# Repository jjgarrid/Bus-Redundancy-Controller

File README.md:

# Bus-Redundancy-Controller
Bus redundancy controller PoC implemented using a FPGA

This project is in a very early stage of design.

The idea comes from an academic paper:

https://www.researchgate.net/publication/262367702_Design_of_redundant_CAN_bus_for_telemetry_and_telecommand_subsystem_of_a_micro-satellite

Design of Redundant CAN Bus for Telemetry and Telecommand Subsystem of a Micro-Satellite

## The idea

Connect several buses common buses (Spacewire, CAN, I2C, SPI...) to a inexpensive, small, low power FPGA (Lattice semi ICE40) that will provide smart switching between different redundant routes (physical traces in the board).

## Constraints / requirements

FPGA needs to be small and integrated in order to be easily added to on board computers and other systems. Good candidates are ICE40LP640 or ICE40LP1K in the package configuration 16-ball WLCSP (1.40 x 1.48 mm). 

Future developments might consider devices with more IO banks.

## Hardware develpment

Either KiCad or Upverter. Probably upverter as it is an online solution.

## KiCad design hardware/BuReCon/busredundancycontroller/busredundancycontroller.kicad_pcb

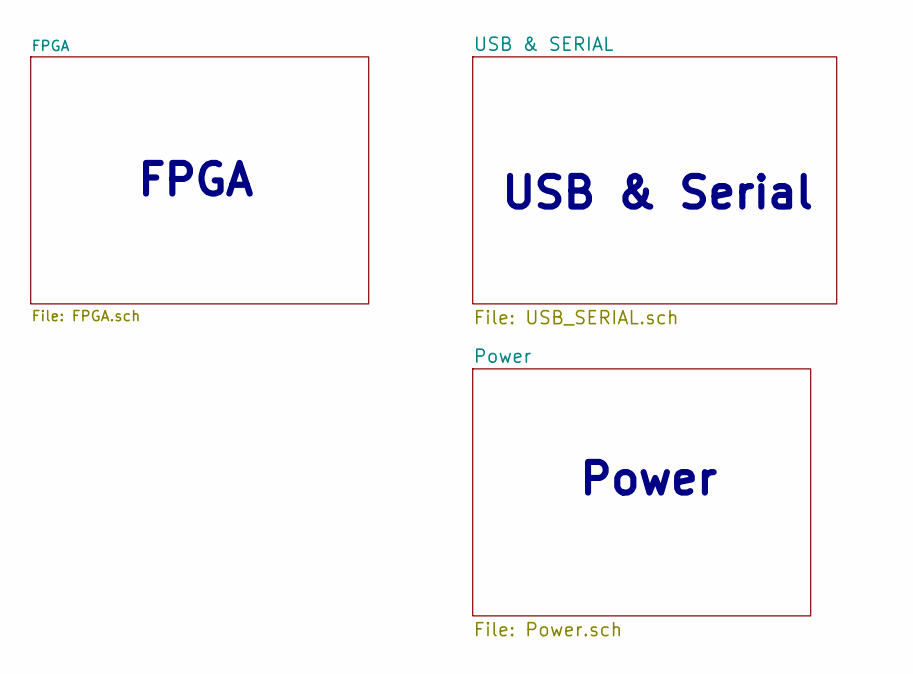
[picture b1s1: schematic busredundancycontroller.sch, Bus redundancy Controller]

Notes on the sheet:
Power
USB & Serial
FPGA

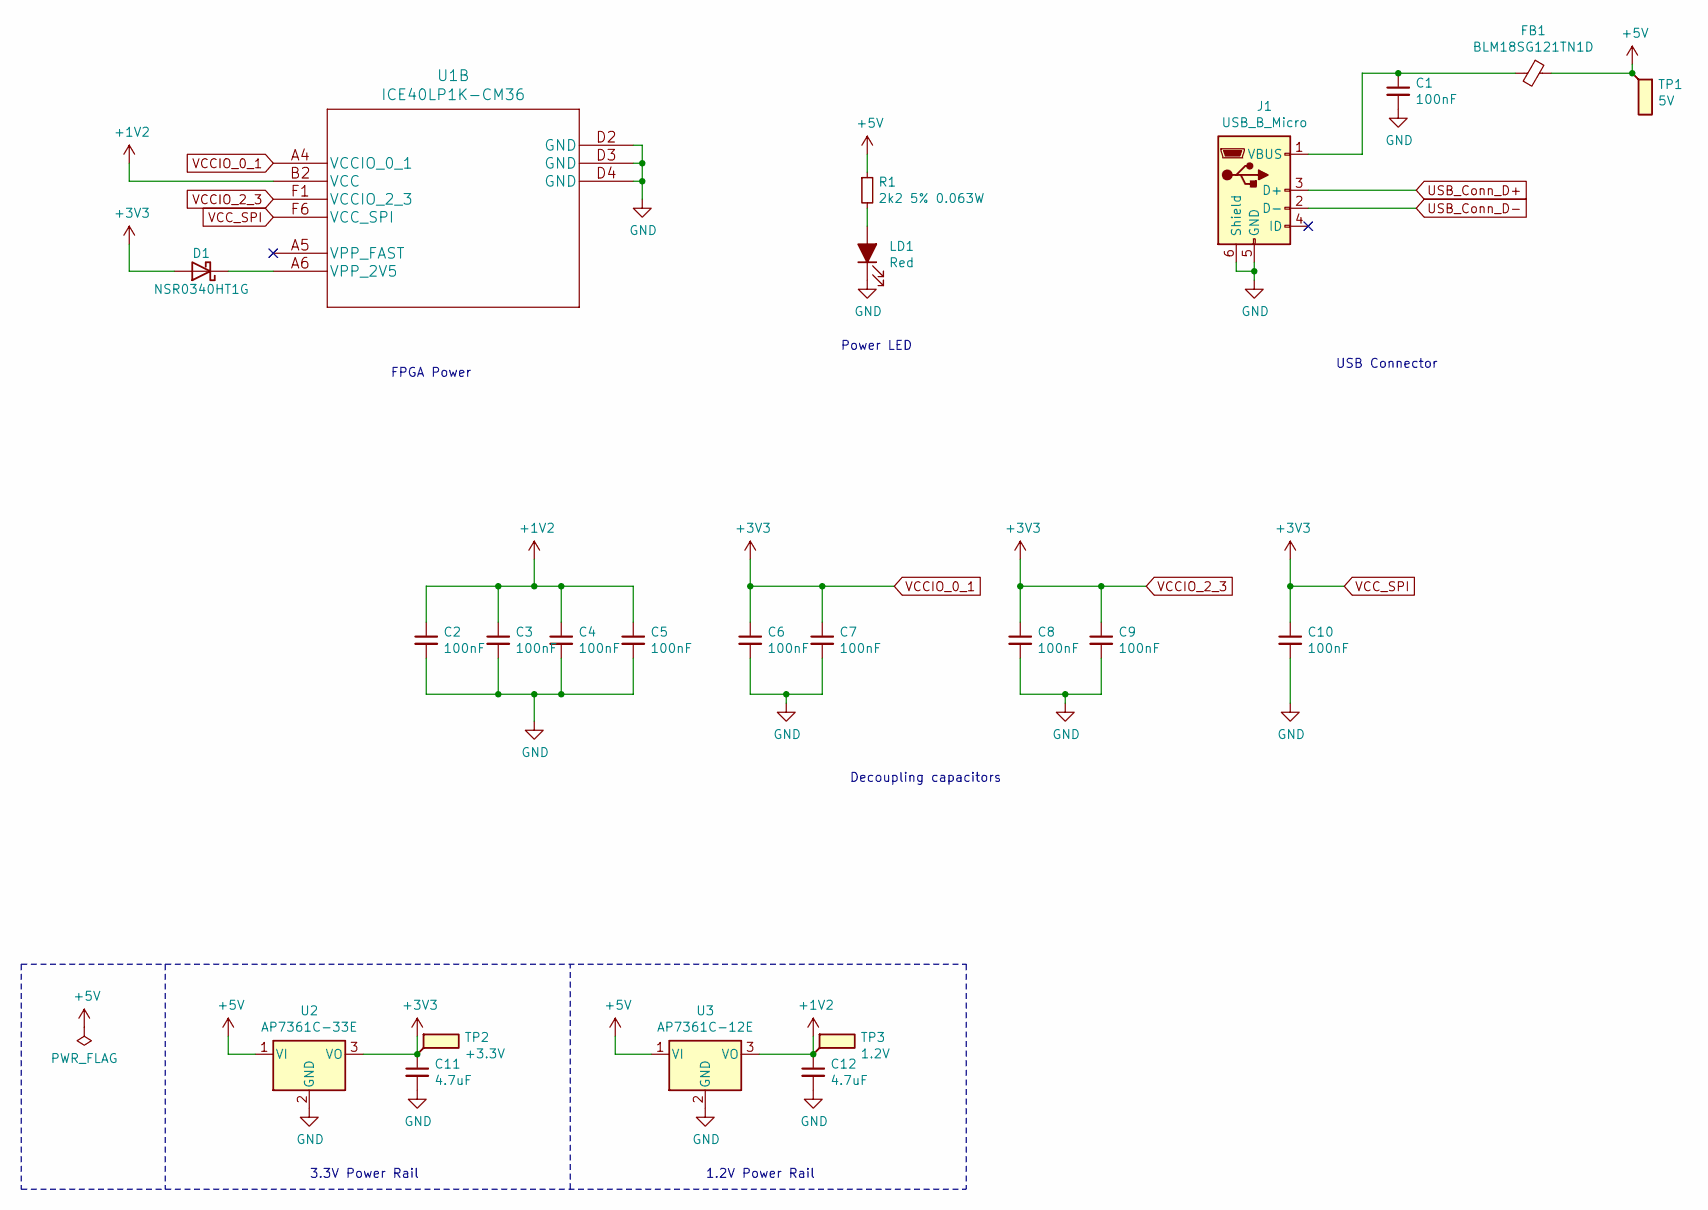
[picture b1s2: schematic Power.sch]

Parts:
C1, C2, C3, C4, C5, C6, C7, C8, C9, C10: 100nF; C_0603_1608Metric
C11, C12: 4.7uF; C_0603_1608Metric
D1: NSR0340HT1G; D_SOD-323
FB1: BLM18SG121TN1D; L_0603_1608Metric
J1: USB_B_Micro; USB_Micro-AB_Molex_47590-0001
LD1: Red; LED_0603_1608Metric
R1: 2k2 5% 0.063W; R_0603_1608Metric
TP1: 5V; TestPoint_Pad_D1.0mm
TP2: +3.3V; TestPoint_Pad_D1.0mm
TP3: 1.2V; TestPoint_Pad_D1.0mm
U1: ICE40LP1K-CM36
U2: AP7361C-33E; SOT-223
U3: AP7361C-12E; SOT-223

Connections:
+1V2: C2.1, C3.1, C4.1, C5.1, C12.1, TP3.1, U1.B2 (VCC), U3.3 (VO)
+5V: FB1.1, R1.1, TP1.1, U2.1 (VI), U3.1 (VI); also elsewhere on the board
GND: C1.2, C2.2, C3.2, C4.2, C5.2, C6.2, C7.2, C8.2, C9.2, C10.2, C11.2, C12.2, J1.5 (GND), J1.6 (Shield), LD1.1 (K), U1.D2 (GND), U1.D3 (GND), U1.D4 (GND), U2.2 (GND), U3.2 (GND); also elsewhere on the board
unnamed: C1.1, FB1.2, J1.1 (VBUS)
unnamed: D1.1 (K), U1.A6 (VPP_2V5)
unnamed: LD1.2 (A), R1.2
USB_Conn_D+: J1.3 (D+); also elsewhere on the board
USB_Conn_D-: J1.2 (D-); also elsewhere on the board

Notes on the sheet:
3.3V Power Rail
1.2V Power Rail
Decoupling capacitors
USB Connector
FPGA Power
Power LED

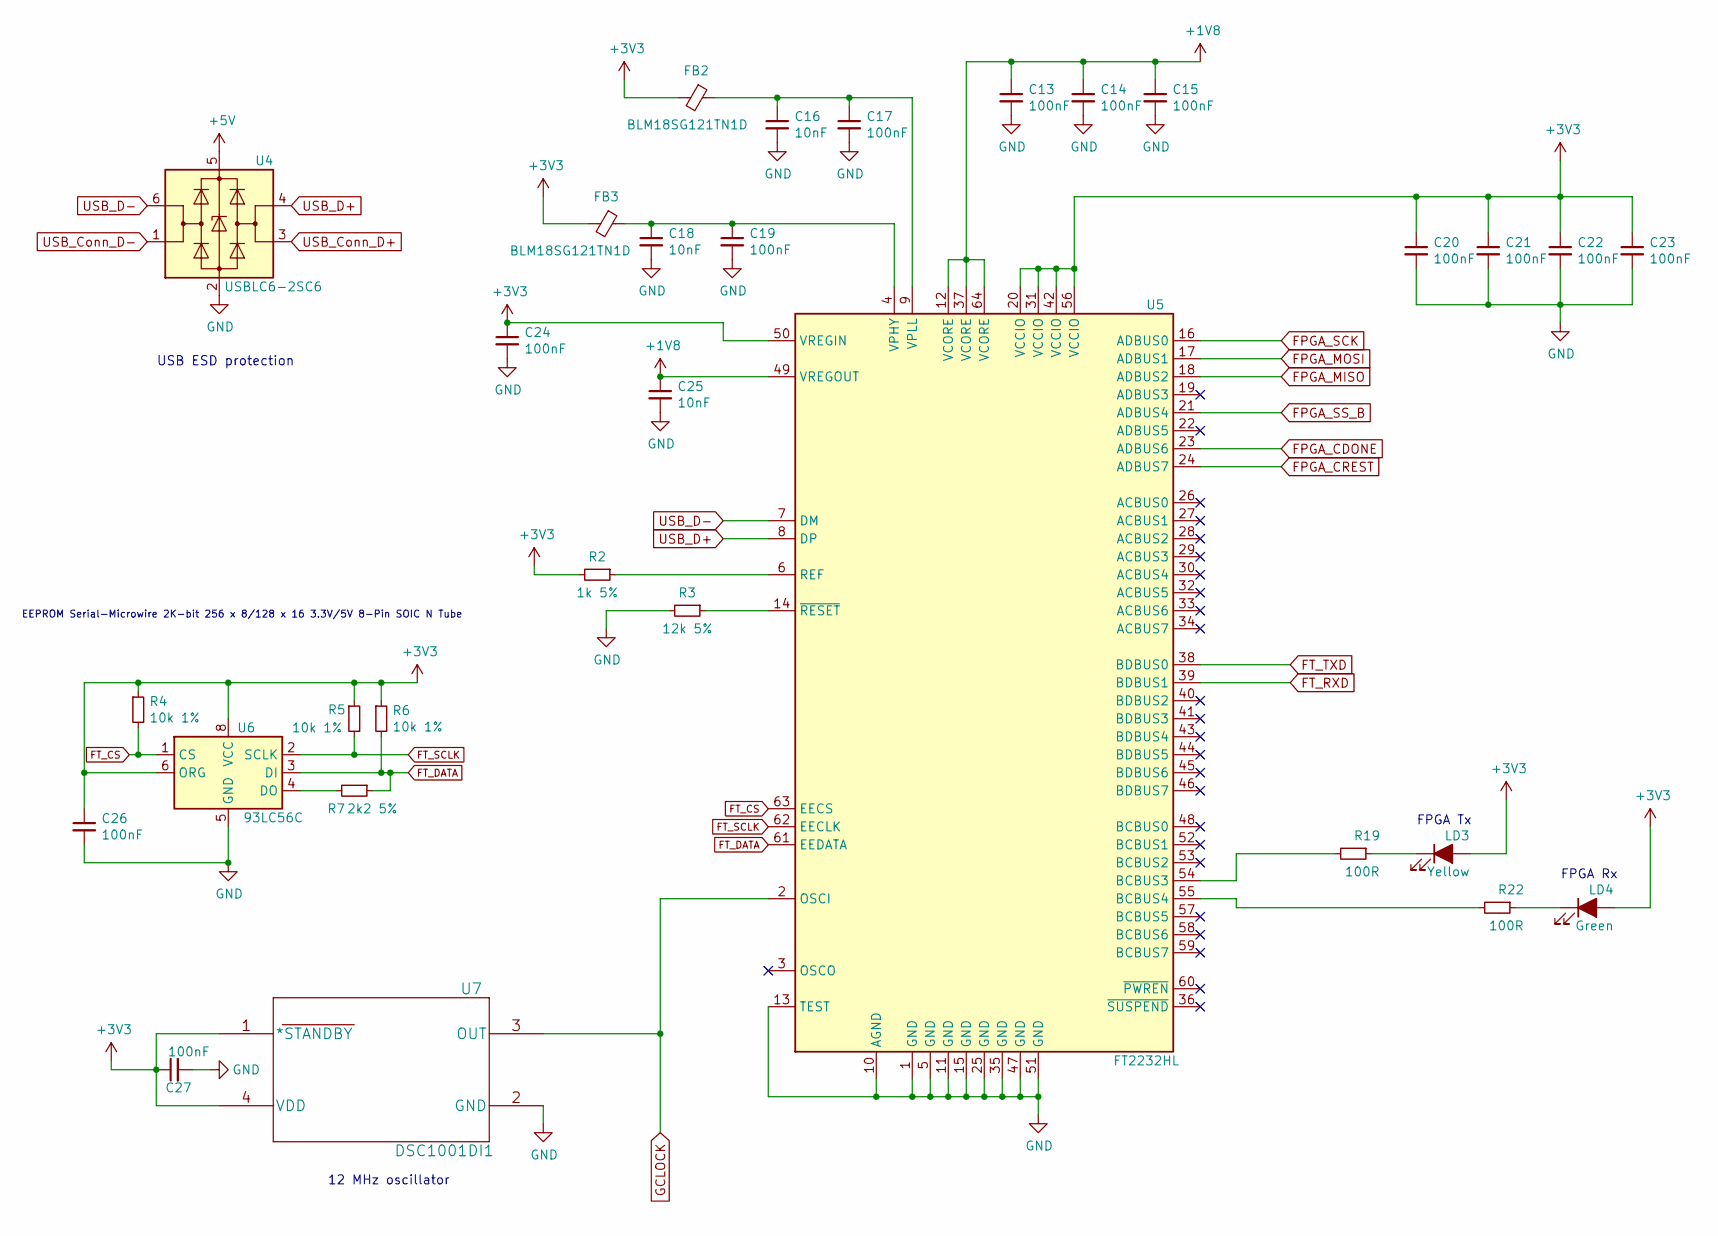
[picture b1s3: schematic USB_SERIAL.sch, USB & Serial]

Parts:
C13, C14, C15, C17, C19, C20, C21, C22, C23, C24, C26, C27: 100nF; C_0603_1608Metric
C16, C18, C25: 10nF; C_0603_1608Metric
FB2, FB3: BLM18SG121TN1D; L_0603_1608Metric
LD3: Yellow; LED_0603_1608Metric
LD4: Green; LED_0603_1608Metric
R2: 1k 5%; R_0603_1608Metric
R3: 12k 5%; R_0603_1608Metric
R4, R5, R6: 10k 1%; R_0603_1608Metric
R7: 2k2 5%; R_0603_1608Metric
R19, R22: 100R; R_0603_1608Metric
U4: USBLC6-2SC6; SOT-23-6
U5: FT2232HL; LQFP-64_10x10mm_P0.5mm
U6: 93LC56C; SOIC-8_3.9x4.9mm_P1.27mm
U7: DSC1001DI1; DSC1001DI1-033.3333T

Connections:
+1V8: C13.1, C14.1, C15.1, C25.1, U5.12 (VCORE), U5.37 (VCORE), U5.49 (VREGOUT), U5.64 (VCORE)
+5V: U4.5 (VBUS); also elsewhere on the board
FPGA_CDONE: U5.23 (ADBUS6); also elsewhere on the board
FPGA_CREST: U5.24 (ADBUS7); also elsewhere on the board
FPGA_MISO: U5.18 (ADBUS2); also elsewhere on the board
FPGA_MOSI: U5.17 (ADBUS1); also elsewhere on the board
FPGA_SCK: U5.16 (ADBUS0); also elsewhere on the board
FPGA_SS_B: U5.21 (ADBUS4); also elsewhere on the board
FT_CS: R4.2, U5.63 (EECS), U6.1 (CS)
FT_DATA: R6.2, R7.1, U5.61 (EEDATA), U6.3 (DI)
FT_SCLK: R5.2, U5.62 (EECLK), U6.2 (SCLK)
GCLOCK: U5.2 (OSCI), U7.3 (OUT); also elsewhere on the board
GND: C13.2, C14.2, C15.2, C16.2, C17.2, C18.2, C19.2, C20.2, C21.2, C22.2, C23.2, C24.2, C25.2, C26.2, C27.2, R3.2, U4.2 (GND), U5.1 (GND), U5.5 (GND), U5.10 (AGND), U5.11 (GND), U5.13 (TEST), U5.15 (GND), U5.25 (GND), U5.35 (GND), U5.47 (GND), U5.51 (GND), U6.5 (GND), U7.2 (GND); also elsewhere on the board
unnamed: C16.1, C17.1, FB2.1, U5.9 (VPLL)
unnamed: C18.1, C19.1, FB3.1, U5.4 (VPHY)
unnamed: LD3.1 (K), R19.1
unnamed: LD4.1 (K), R22.1
unnamed: R2.1, U5.6 (REF)
unnamed: R3.1, U5.14 (~RESET)
unnamed: R7.2, U6.4 (DO)
unnamed: R19.2, U5.54 (BCBUS3)
unnamed: R22.2, U5.55 (BCBUS4)
USB_Conn_D+: U4.3 (I/O2); also elsewhere on the board
USB_Conn_D-: U4.1 (I/O1); also elsewhere on the board
USB_D+: U4.4 (I/O2), U5.8 (DP)
USB_D-: U4.6 (I/O1), U5.7 (DM)

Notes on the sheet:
USB ESD protection
12 MHz oscillator
EEPROM Serial-Microwire 2K-bit 256 x 8/128 x 16 3.3V/5V 8-Pin SOIC N Tube
FPGA Tx
FPGA Rx

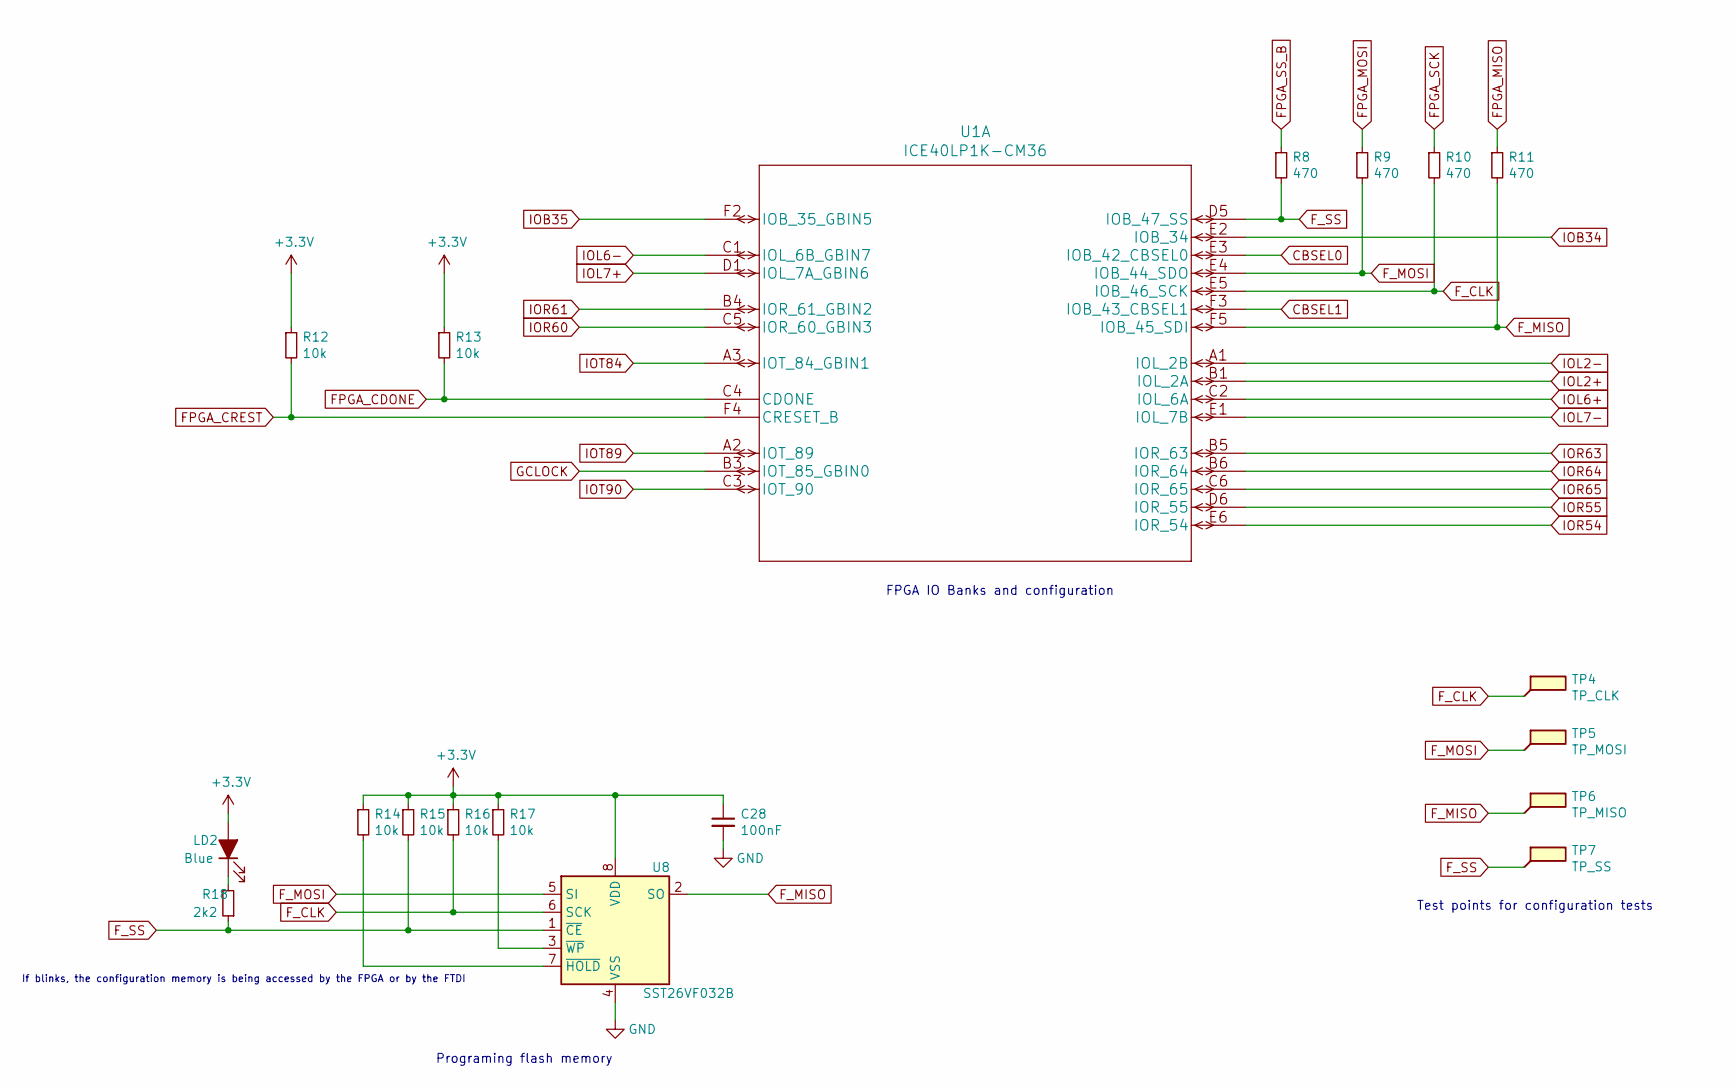
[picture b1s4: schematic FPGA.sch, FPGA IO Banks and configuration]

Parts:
C28: 100nF
LD2: Blue; LED_0201_0603Metric
R8, R9, R10, R11: 470
R12, R13, R14, R15, R16, R17: 10k
R18: 2k2
TP4: TP_CLK; TestPoint_Plated_Hole_D3.0mm
TP5: TP_MOSI; TestPoint_Plated_Hole_D3.0mm
TP6: TP_MISO; TestPoint_Plated_Hole_D3.0mm
TP7: TP_SS; TestPoint_Plated_Hole_D3.0mm
U1: ICE40LP1K-CM36
U8: SST26VF032B; SOIC-8_5.275x5.275mm_P1.27mm

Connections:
CBSEL0: U1.E3 (IOB_42_CBSEL0); also elsewhere on the board
CBSEL1: U1.F3 (IOB_43_CBSEL1); also elsewhere on the board
FPGA_CDONE: R13.2, U1.C4 (CDONE); also elsewhere on the board
FPGA_CREST: R12.2, U1.F4 (CRESET_B); also elsewhere on the board
FPGA_MISO: R11.1; also elsewhere on the board
FPGA_MOSI: R9.1; also elsewhere on the board
FPGA_SCK: R10.1; also elsewhere on the board
FPGA_SS_B: R8.1; also elsewhere on the board
F_CLK: R10.2, R16.2, TP4.1, U1.E5 (IOB_46_SCK), U8.6 (SCK)
F_MISO: R11.2, TP6.1, U1.F5 (IOB_45_SDI), U8.2 (SO)
F_MOSI: R9.2, TP5.1, U1.E4 (IOB_44_SDO), U8.5 (SI)
F_SS: R8.2, R15.2, R18.1, TP7.1, U1.D5 (IOB_47_SS), U8.1 (~CE)
GCLOCK: U1.B3 (IOT_85_GBIN0); also elsewhere on the board
GND: C28.2, U8.4 (VSS); also elsewhere on the board
IOB35: U1.F2 (IOB_35_GBIN5); also elsewhere on the board
IOL2+: U1.B1 (IOL_2A); also elsewhere on the board
IOL2-: U1.A1 (IOL_2B); also elsewhere on the board
IOL6+: U1.C2 (IOL_6A); also elsewhere on the board
IOL6-: U1.C1 (IOL_6B_GBIN7); also elsewhere on the board
IOL7+: U1.D1 (IOL_7A_GBIN6); also elsewhere on the board
IOL7-: U1.E1 (IOL_7B); also elsewhere on the board
IOR54: U1.E6 (IOR_54); also elsewhere on the board
IOR55: U1.D6 (IOR_55); also elsewhere on the board
IOR60: U1.C5 (IOR_60_GBIN3); also elsewhere on the board
IOR61: U1.B4 (IOR_61_GBIN2); also elsewhere on the board
IOR63: U1.B5 (IOR_63); also elsewhere on the board
IOR64: U1.B6 (IOR_64); also elsewhere on the board
IOT84: U1.A3 (IOT_84_GBIN1); also elsewhere on the board
IOT89: U1.A2 (IOT_89); also elsewhere on the board
IOT90: U1.C3 (IOT_90); also elsewhere on the board
unnamed: LD2.1 (K), R18.2
unnamed: R14.2, U8.7 (~HOLD~)
unnamed: R17.2, U8.3 (~WP~)

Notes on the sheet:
Programing flash memory
FPGA IO Banks and configuration
Test points for configuration tests
If blinks, the configuration memory is being accessed by the FPGA or by the FTDI

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
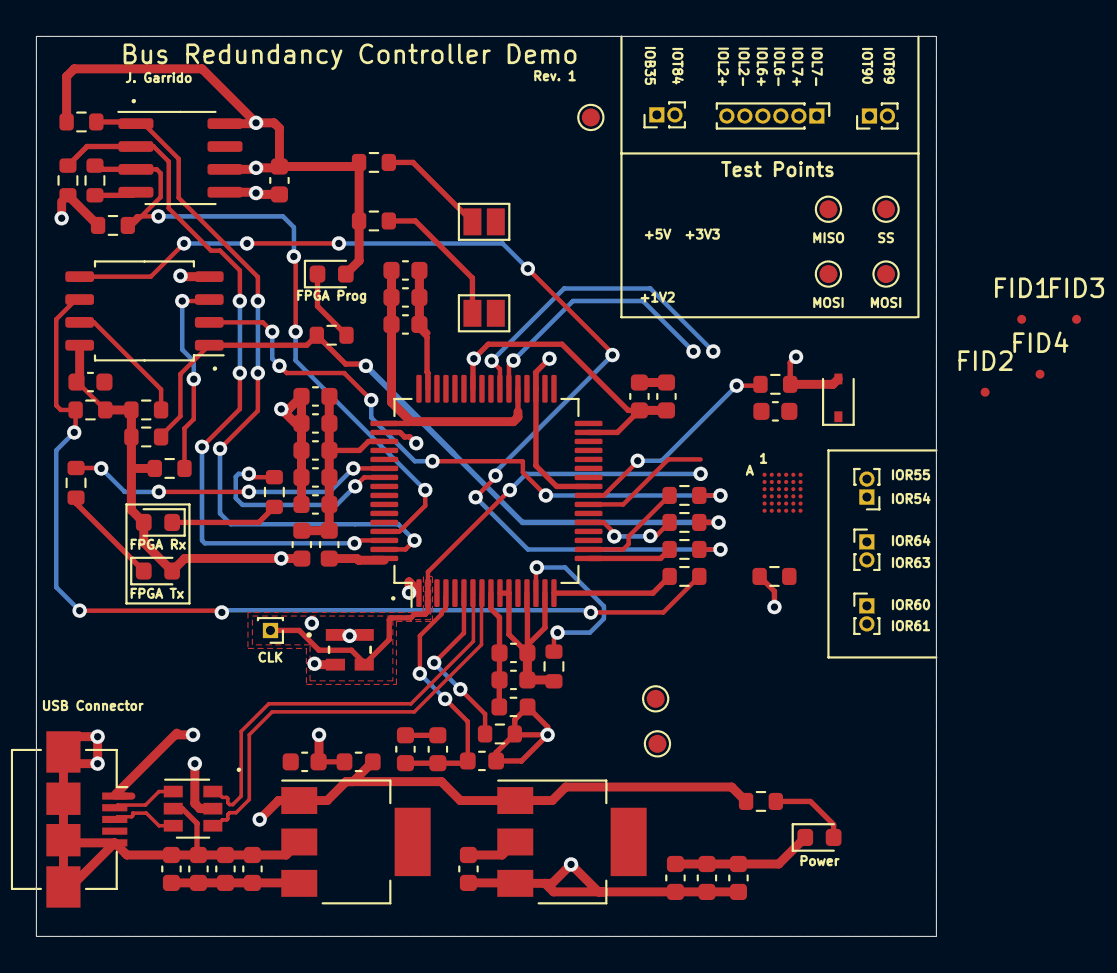
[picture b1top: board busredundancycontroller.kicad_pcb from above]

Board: 4 copper layers, 50.0 x 50.0 mm, 87 parts (0 on the bottom side), 60 nets.

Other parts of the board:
FID1, FID2, FID3, FID4: Fiducial; Fiducial_0.5mm_Mask1.5mm
J2: Clock Output; PinHeader_1x01_P1.00mm_Vertical
J3: Differential IO; PinHeader_1x06_P1.00mm_Vertical
J4: Input/Output 1; PinHeader_1x02_P1.00mm_Vertical
J5: Input/Output 2; PinHeader_1x02_P1.00mm_Vertical
J6: Input/Output 3; PinHeader_1x02_P1.00mm_Vertical
J7: Input/Output 4; PinHeader_1x02_P1.00mm_Vertical
J8: Input/Output 5; PinHeader_1x02_P1.00mm_Vertical
JP1: CBSEL0; SolderJumper-2_P1.3mm_Open_Pad1.0x1.5mm
JP2: CBSEL1; SolderJumper-2_P1.3mm_Open_Pad1.0x1.5mm
R20, R21: 10k; R_0603_1608Metric

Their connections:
CBSEL0: JP1.2; also elsewhere on the board
CBSEL1: JP2.2; also elsewhere on the board
GCLOCK: J2.1; also elsewhere on the board
IOB35: J8.1; also elsewhere on the board
IOL2+: J3.6; also elsewhere on the board
IOL2-: J3.5; also elsewhere on the board
IOL6+: J3.4; also elsewhere on the board
IOL6-: J3.3; also elsewhere on the board
IOL7+: J3.2; also elsewhere on the board
IOL7-: J3.1; also elsewhere on the board
IOR54: J5.1; also elsewhere on the board
IOR55: J5.2; also elsewhere on the board
IOR60: J6.1; also elsewhere on the board
IOR61: J6.2; also elsewhere on the board
IOR63: J7.2; also elsewhere on the board
IOR64: J7.1; also elsewhere on the board
IOT84: J8.2; also elsewhere on the board
IOT89: J4.2; also elsewhere on the board
IOT90: J4.1; also elsewhere on the board
unnamed: JP1.1, R21.2
unnamed: JP2.1, R20.2

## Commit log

2020-09-14 Initial version of the README file
2020-09-14 Initial commit. Mostly empty and test code to verify toolchain.
2020-09-14 Initial commit on the HW design. Empty project with the device from upverter
2020-10-03 Added support documentation
    Added design support documentation
2020-10-04 Power section
2020-10-04 Added Power rails and USB
2020-10-04 Updated PDF schematics
2020-10-05 FT2232 power and ESD
2020-10-05 Schematics update
2020-10-13 House Keeping
    House keeping
2020-10-14 FPGA configuration
2020-10-14 Replace the FT2232HL with the correct datasheet
2020-10-14 Cleanup and IO banks
2020-10-14 Added 12 MHz oscillator datasheet
2020-10-15 Connectors and RS232
2020-10-16 Footprints, Initial PCB
2020-10-18 PCB preliminary placement
2020-10-18 PBC placement. Silk
2020-10-24 Fixed some DRC errors. Added pour zones
2020-10-24 Correct nets in every layer
2020-10-24 Routing power
2020-11-15 last minute changes

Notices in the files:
parts and their libraries:
Copyright 2016 Accelerated Designs. All rights reserved.
